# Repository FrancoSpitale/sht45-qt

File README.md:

# SHT45-QT — precision temperature & humidity breakout

A small open-source breakout for the **Sensirion SHT45** (±1.0 % RH, ±0.1 °C) with
**Qwiic / STEMMA QT** connectors, designed in **KiCad 9**. 25.4 × 20.3 mm, 2 layers,
ready to fabricate at JLCPCB (gerbers included).

| Top | Bottom |
|---|---|
|  |  |

Schematic: [docs/schematic.svg](docs/schematic.svg) · Source: [hardware/](hardware/)

## Features

- Sensirion **SHT4x** family (SHT40 / SHT41 / SHT45 are drop-in compatible, same DFN-4 footprint)
- Two **JST SH 4-pin** (Qwiic/STEMMA QT) connectors for daisy-chaining, plus a
  0.1" **GND · 3V3 · SDA · SCL** header for breadboards
- I²C address **0x44** (fixed by the chip)
- 10 k I²C pull-ups with a **cuttable solder jumper** (JP1)
- Thermally isolated sensor island (milled U-slot + copper keepout)
- 2 × M2.5 mounting holes

## Design decisions

**Thermal isolation slot.** Temperature sensors don't measure air — they measure
their own die. Anything that couples the die to the PCB's thermal mass (copper
pours, nearby components) slows response and biases the reading. The sensor sits
on a small tongue isolated by a 1.2 mm milled U-slot, connected only through two
narrow bridges that carry the four traces. Copper pour is excluded from the
tongue and bridges on both layers; only the four signal/power traces (0.2 mm)
cross over.

**No power LED.** A power LED burns 1–3 mA a few millimetres from a sensor specified
to ±0.1 °C — that's measurable self-heating, and it ruins battery budgets on a part
that idles at well under 1 µA. If you need a visual heartbeat, blink it from the host.

**Pull-ups behind a solder jumper.** Qwiic chains accumulate pull-ups: every board
in the chain adds its pair in parallel. JP1 ships bridged (pull-ups enabled) —
cut the trace between the pads to disable them when your controller board or
another breakout already provides them. 10 k was chosen over the more common
4.7 k so that two or three boards left enabled by accident still keep the bus
within spec instead of overloading the drivers.

**Decoupling cap just off the island.** The 100 nF cap sits ~4.5 mm from the sensor,
on the main board side of the slot, instead of on the tongue. Trade-off: Sensirion
asks for the cap "close to the sensor", but a ceramic cap on the tongue adds thermal
mass exactly where we're trying to remove it. At SHT4x supply currents (µA idle,
sub-mA peaks during measurement) 4.5 mm of 0.2 mm trace is electrically negligible,
so the thermal argument wins.

**Routing.** Solid GND pours on both layers with stitching vias; the bottom layer
stays a nearly unbroken plane except for a short bus corridor to the header. Signals
enter the sensor island from the top row of pads, power from the bottom row, so no
net ever crosses another on the tongue.

## Specs

| Parameter | Value |
|---|---|
| Sensor | SHT45 (SHT40/41 compatible) |
| Accuracy (SHT45) | ±1.0 % RH, ±0.1 °C (typ.) |
| Supply | 1.08 – 3.6 V (board intended for 3.3 V Qwiic) |
| Interface | I²C, address 0x44, up to 1 MHz |
| Board | 25.4 × 20.3 mm, 2-layer, 1.6 mm FR-4 |
| Min track/clearance used | 0.20 mm / 0.20 mm (JLCPCB standard is 0.127 mm) |
| Mounting | 2 × M2.5 |

## Fabrication

`fabrication/sht45-qt-gerbers-jlcpcb.zip` uploads directly to JLCPCB:
2 layers, 1.6 mm, any finish (ENIG recommended if you hand-solder the DFN),
standard stackup. The internal U-slot is 1.2 mm wide — above JLCPCB's 0.8 mm
minimum for routed slots. `sht45-qt-bom.csv` and `sht45-qt-pos.csv` are ready
for the assembly service (add LCSC part numbers at order time).

The DFN-4 sensor is hand-solderable with hot air and gel flux; everything else
is 0603 or larger.

## Using it

Any SHT4x library works, e.g. [Sensirion arduino-i2c-sht4x](https://github.com/Sensirion/arduino-i2c-sht4x)
or [Adafruit_SHT4x](https://github.com/adafruit/Adafruit_SHT4X):

```cpp
#include <Adafruit_SHT4x.h>
Adafruit_SHT4x sht4;

void setup() {
  sht4.begin();                       // 0x44
  sht4.setPrecision(SHT4X_HIGH_PRECISION);
}

void loop() {
  sensors_event_t rh, t;
  sht4.getEvent(&rh, &t);
  // t.temperature (°C), rh.relative_humidity (%RH)
  delay(1000);
}
```

A ready-to-flash version of this sketch lives in
[examples/arduino/sht45_qt_basic](examples/arduino/sht45_qt_basic/sht45_qt_basic.ino).

For fast response, mount the board sensor-edge up, away from heat sources, and
give the slot free airflow on both sides.

## Verification

- ERC: 0 errors, 0 warnings ([hardware/erc.rpt](hardware/erc.rpt))
- DRC: 0 violations **including warnings**, 0 unconnected items,
  0 schematic-parity issues ([hardware/drc.rpt](hardware/drc.rpt))
- Pinout cross-checked against the [Sensirion SHT4x datasheet](https://sensirion.com/resource/datasheet/sht4x)

## Repository layout

```
hardware/     KiCad 9 project (schematic, PCB, ERC/DRC reports)
fabrication/  Gerbers zip (JLCPCB), BOM, pick & place
examples/     Arduino example sketch
docs/         Renders and schematic SVG
```

## License

MIT — see [LICENSE](LICENSE). Hardware provided as-is, no warranty; review before
fabricating.

---
*Designed by Franco Spitale, 2026. Rev 1.0 — not yet fabricated; if you build one,
open an issue with your results.*

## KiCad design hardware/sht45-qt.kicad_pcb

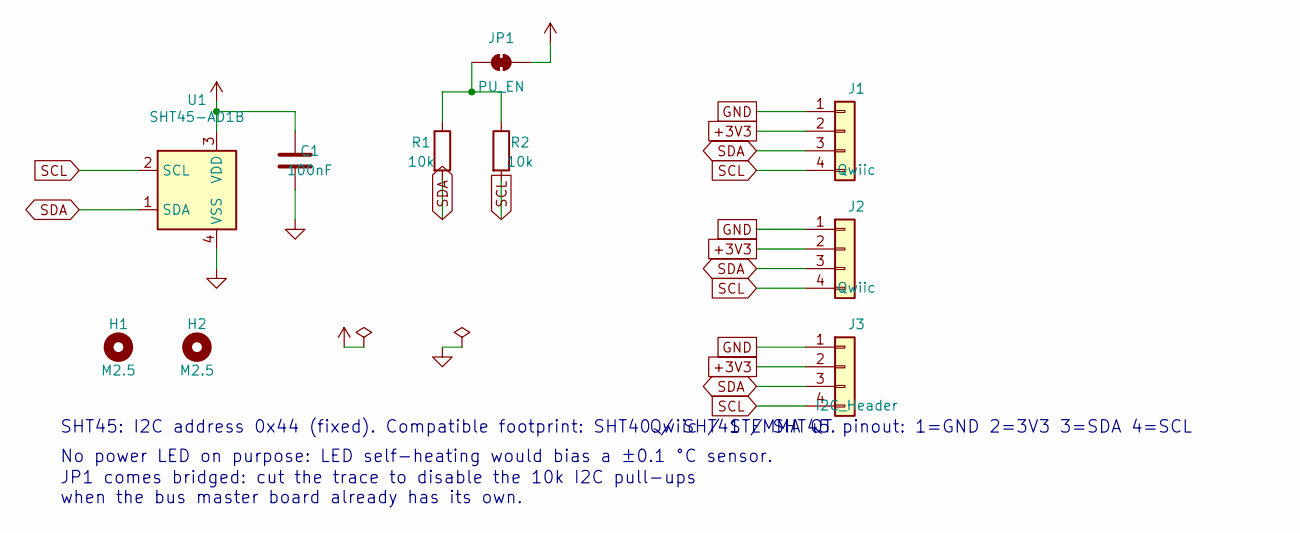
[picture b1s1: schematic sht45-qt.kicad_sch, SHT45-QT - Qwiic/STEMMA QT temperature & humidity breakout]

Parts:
C1: 100nF; C_0603_1608Metric; MPN CL10B104KB8NNNC
H1, H2: M2.5; MountingHole_2.7mm_M2.5
J1, J2: Qwiic; JST_SH_SM04B-SRSS-TB_1x04-1MP_P1.00mm_Horizontal; MPN SM04B-SRSS-TB(LF)(SN)
J3: I2C_Header; PinHeader_1x04_P2.54mm_Vertical
JP1: PU_EN; SolderJumper-2_P1.3mm_Bridged_RoundedPad1.0x1.5mm
R1, R2: 10k; R_0603_1608Metric; MPN RC0603FR-0710KL
U1: SHT45-AD1B; Sensirion_DFN-4_1.5x1.5mm_P0.8mm_SHT4x_NoCentralPad; MPN SHT45-AD1B-R2

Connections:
+3V3: C1.1, J1.2, J2.2, J3.2, JP1.2 (B), U1.3 (VDD)
GND: C1.2, J1.1, J2.1, J3.1, U1.4 (VSS)
unnamed: JP1.1 (A), R1.1, R2.1
SCL: J1.4, J2.4, J3.4, R2.2, U1.2 (SCL)
SDA: J1.3, J2.3, J3.3, R1.2, U1.1 (SDA)

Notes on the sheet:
SHT45: I2C address 0x44 (fixed). Compatible footprint: SHT40 / SHT41 / SHT45.
No power LED on purpose: LED self-heating would bias a ±0.1 °C sensor.
JP1 comes bridged: cut the trace to disable the 10k I2C pull-ups when the bus master board already has its own.
Qwiic / STEMMA QT pinout: 1=GND 2=3V3 3=SDA 4=SCL

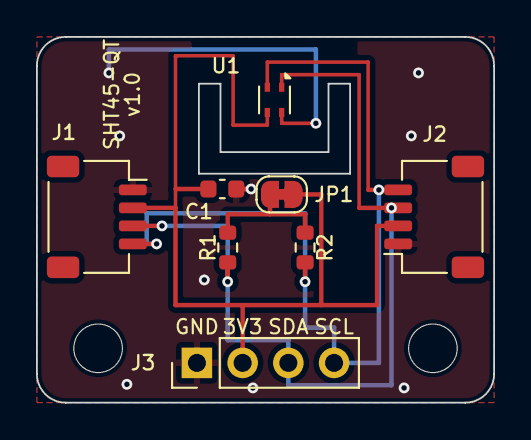
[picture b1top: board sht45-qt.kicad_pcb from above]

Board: 2 copper layers, 25.4 x 20.3 mm, 10 parts (0 on the bottom side), 5 nets.

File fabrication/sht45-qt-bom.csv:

"Designator","Value","MPN","Footprint","Qty"
"C1","100nF","CL10B104KB8NNNC","Capacitor_SMD:C_0603_1608Metric","1"
"J1,J2","Qwiic","SM04B-SRSS-TB(LF)(SN)","Connector_JST:JST_SH_SM04B-SRSS-TB_1x04-1MP_P1.00mm_Horizontal","2"
"J3","I2C_Header","","Connector_PinHeader_2.54mm:PinHeader_1x04_P2.54mm_Vertical","1"
"R1,R2","10k","RC0603FR-0710KL","Resistor_SMD:R_0603_1608Metric","2"
"U1","SHT45-AD1B","SHT45-AD1B-R2","Sensor_Humidity:Sensirion_DFN-4_1.5x1.5mm_P0.8mm_SHT4x_NoCentralPad","1"
